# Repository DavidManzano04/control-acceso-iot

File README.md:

# Control de acceso IoT con RFID — UCEVA

Trabajo de grado **"Sistema inteligente de gestión y control de acceso al campus universitario de la UCEVA basado en tecnología IoT y de identificación automática"** (Ingeniería Electrónica, Unidad Central del Valle del Cauca).

El sistema registra la entrada y salida de los docentes de tiempo completo y ocasionales con lectores RFID, y verifica en tiempo real si cumplen su horario.

## Cómo funciona

```
Lector de ENTRADA ─┐                                           ┌─> SQLite
 (ESP32+Hikvision) │                                           │
                   ├──MQTT/TLS──> HiveMQ Cloud ──> Backend Flask
Lector de SALIDA  ─┘     ^                            │        │
 (ESP32+Hikvision)       └── permitido / denegado ────┘        └─> Dashboard web en vivo
                                                                   (Socket.IO)
```

1. El lector lee la tarjeta por Wiegand, firma la lectura con HMAC-SHA256 y la publica por MQTT sobre TLS.
2. El backend valida la firma, identifica al docente y compara la hora con su horario.
3. El lector muestra la respuesta (LED, pito y LCD) y el registro aparece al instante en el dashboard.
4. Si se cae la red, el lector guarda las lecturas y las envía cuando vuelve la conexión.

## Estructura

| Carpeta | Contenido |
| --- | --- |
| [`hardware/`](hardware) | PCB propia del nodo en KiCad: ESP32-S3, alimentación de 12 V, USB-C e interfaz Wiegand protegida, con gerbers para JLCPCB |
| [`firmware/`](firmware) | Firmware del nodo lector: ESP32, lector Hikvision por Wiegand 34, MQTT/TLS, OTA y modo sin conexión (C++, PlatformIO) |
| [`plataforma-web/`](plataforma-web) | Backend y dashboard: gestión de docentes y horarios, asistencia en tiempo real, reportes y administración de lectores (Python, Flask) |

Cada carpeta tiene su propio README con los detalles y cómo ejecutarla.

## Tecnologías

- **Hardware:** ESP32 / ESP32-S3 · lector RFID Hikvision (Wiegand 34) · LCD I2C · PCB propia diseñada en KiCad
- **Firmware:** C++ · Arduino framework · PlatformIO · LittleFS · ArduinoJson
- **Comunicación:** MQTT sobre TLS · HiveMQ Cloud · HMAC-SHA256
- **Backend y web:** Python · Flask · Flask-SocketIO · SQLite · JWT · HTML/CSS/JavaScript

> Este repositorio no incluye credenciales, la base de datos ni datos personales del prototipo. Cada parte trae un archivo de ejemplo para configurar los tuyos.

## Autores

- David Felipe Manzano Aldana
- David Santiago Vallejo Rodríguez

Ingeniería Electrónica — Unidad Central del Valle del Cauca (UCEVA), 2026.

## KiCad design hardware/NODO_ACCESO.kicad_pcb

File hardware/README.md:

# Hardware — PCB del nodo lector (v1.1)

PCB propia del nodo de control de acceso, diseñada en **KiCad**. Integra el ESP32-S3, la alimentación desde 12 V y la interfaz con el lector Hikvision por Wiegand, lista para fabricar en JLCPCB.

## Características

- **Microcontrolador:** ESP32-S3-WROOM-1-N16R8 (16 MB flash, 8 MB PSRAM), con botones de RESET y BOOT
- **Alimentación:** entrada de 12 V por bornera con fusible PTC de 1,1 A, diodo TVS SMBJ15CA y protección contra polaridad inversa; regulador conmutado AP63205 a 5 V y LDO AP7361C a 3,3 V
- **USB-C** para programación y alimentación, con protección ESD USBLC6-2SC6; diodos Schottky que eligen solos entre los 5 V del regulador y los del USB
- **Interfaz con el lector Hikvision (Wiegand):** W0, W1 y TAMPER adaptados de 5 V a 3,3 V con transistores BSS138; salidas LED verde, LED rojo y BEEP hacia el lector; protección ESD SRV05-4 en todas las líneas del lector
- **Conectores:** borneras de 5,08 mm para 12 V, lector y control del lector; header UART0 y header de expansión con 4 GPIO libres
- LEDs de encendido y de estado
- Placa de 2 capas, 82 × 70 mm, 1,6 mm de espesor
- La versión 1.1 no incluye actuadores (relé, cerradura ni talanquera): el nodo solo registra y da la respuesta en el lector

## Archivos

| Archivo | Contenido |
| --- | --- |
| `NODO_ACCESO.kicad_pro` / `.kicad_sch` / `.kicad_pcb` | Proyecto de KiCad (esquemático y PCB) |
| `Esquematico_NODO_ACCESO.pdf` | Esquemático en PDF, para verlo sin KiCad |
| `BOM_NODO_ACCESO.csv` | Lista de materiales con referencias LCSC |
| `fabricacion/` | Gerbers, BOM y archivo de posiciones (CPL) para pedir la placa ensamblada en JLCPCB |

## Nota sobre el firmware

El [firmware](../firmware) actual corre en el prototipo armado con un ESP32 DevKit. Para esta PCB con el ESP32-S3 hay que ajustar la asignación de pines según el esquemático.

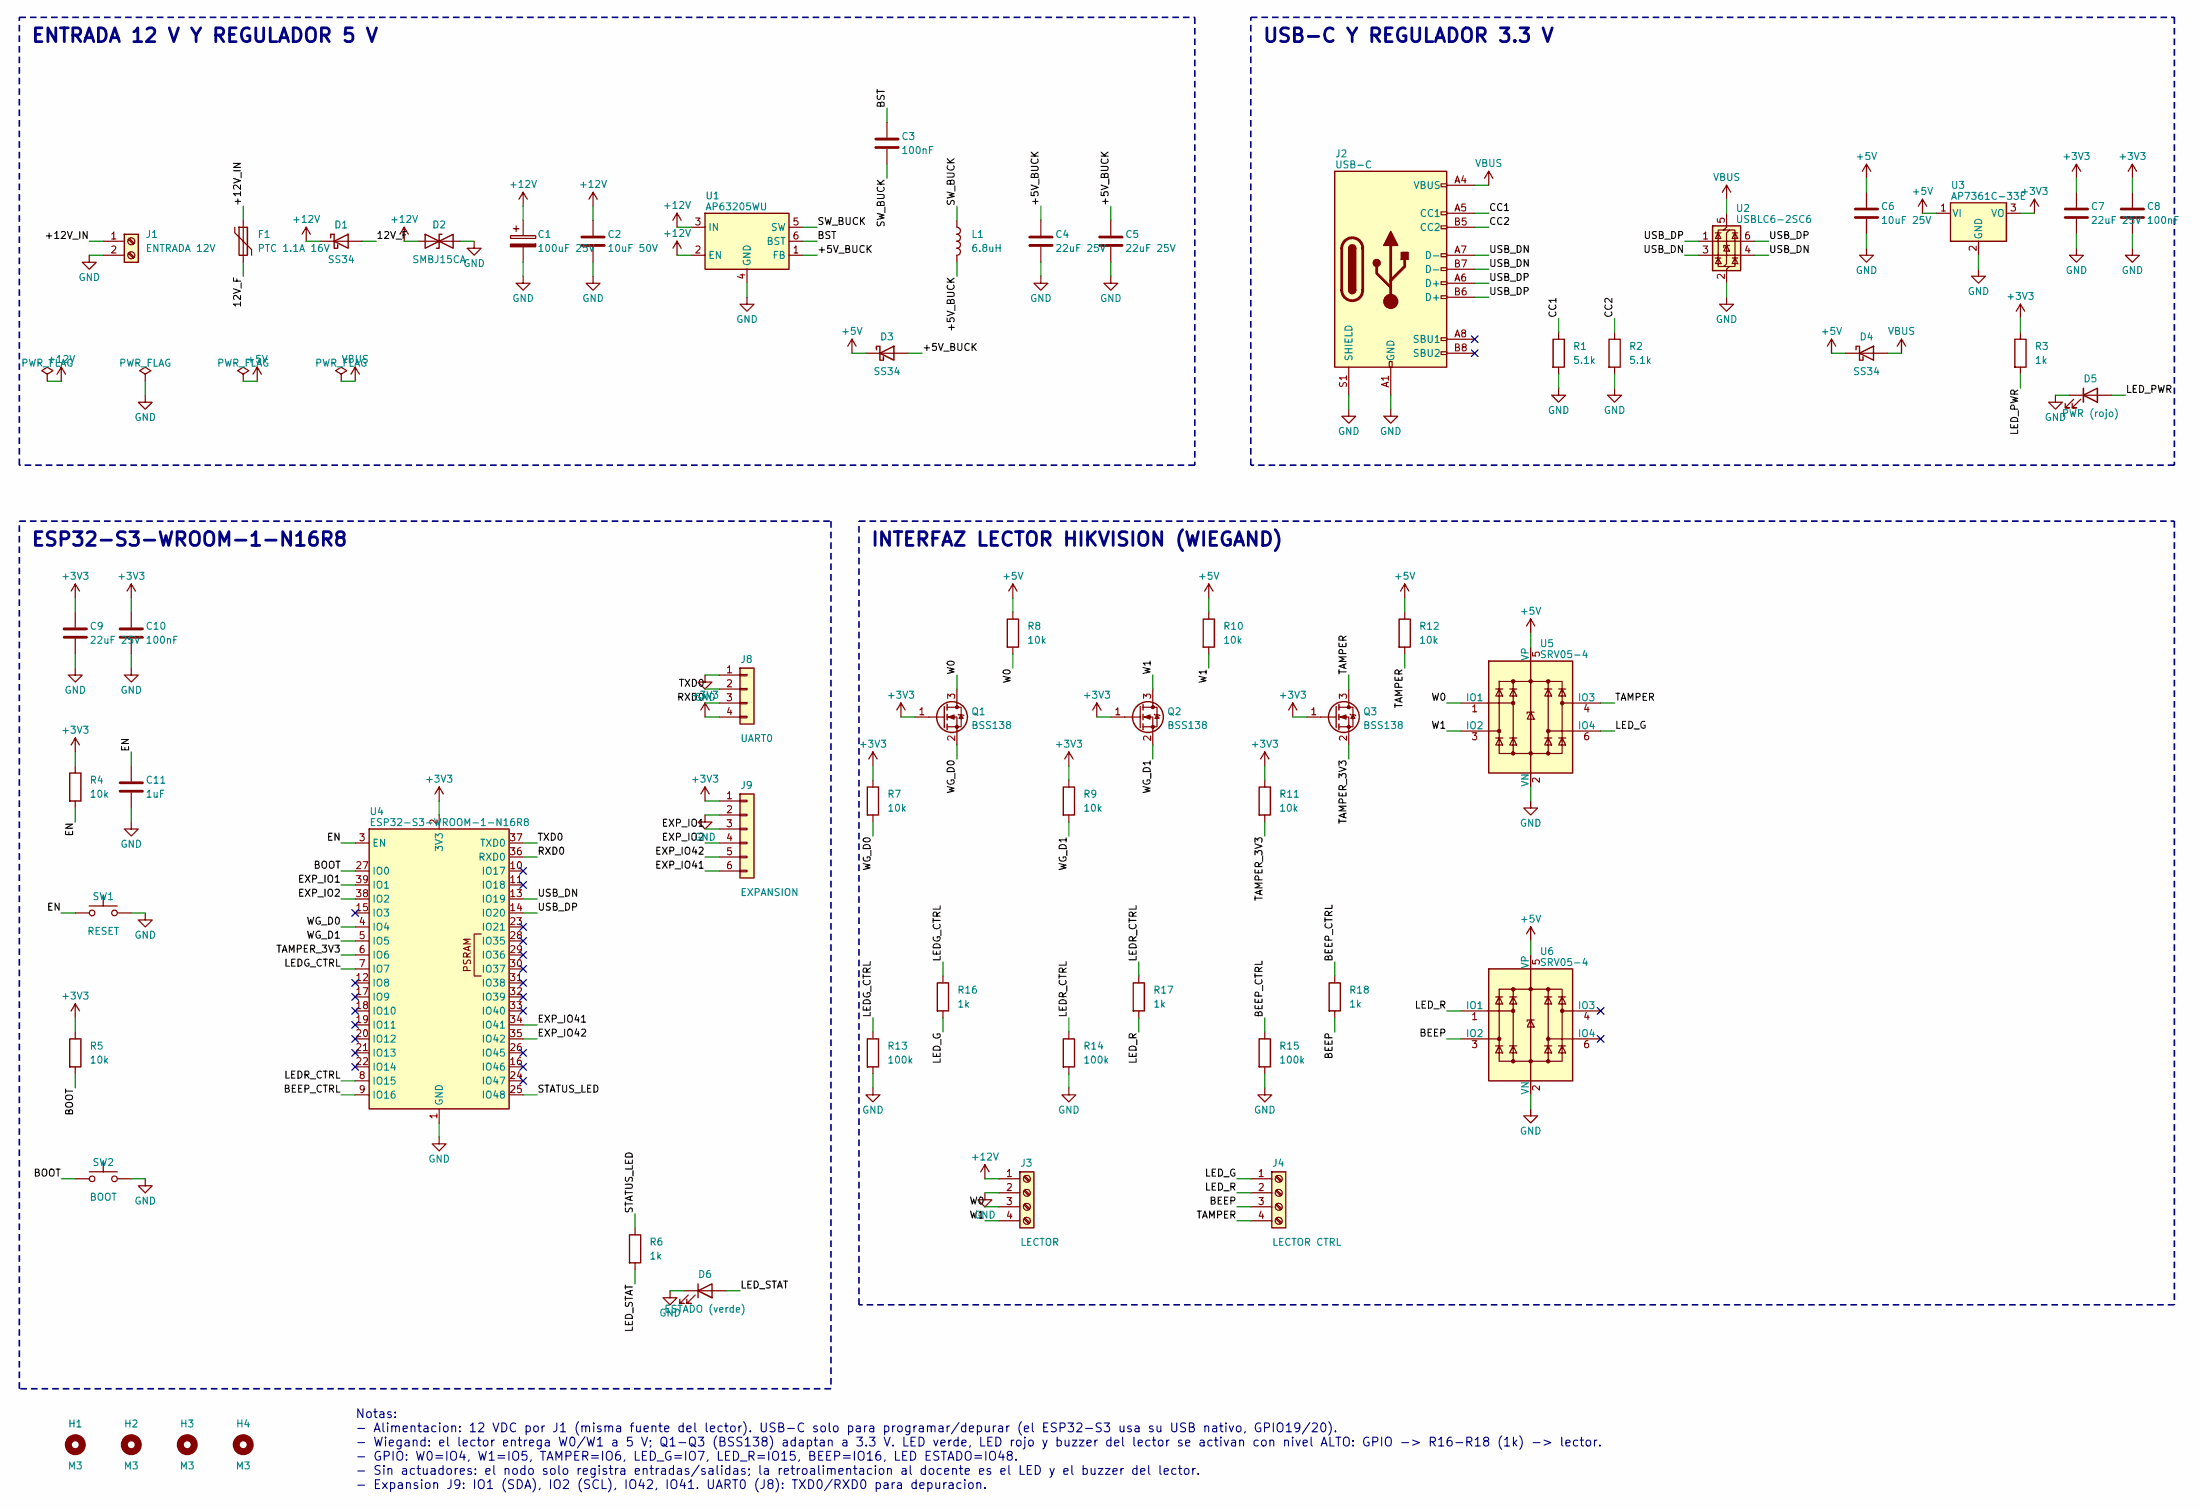
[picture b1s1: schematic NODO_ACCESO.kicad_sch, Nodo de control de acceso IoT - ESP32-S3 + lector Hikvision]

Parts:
C1: 100uF 25V; CP_Elec_6.3x7.7; MPN Aluminio SMD 100 uF 25 V 6.3 mm; LCSC C2941301
C2: 10uF 50V; C_1206_3216Metric; MPN X5R 1206 10 uF 25 V; LCSC C13585
C3, C8, C10: 100nF; C_0603_1608Metric; LCSC C14663
C4, C5: 22uF 25V; C_1206_3216Metric; LCSC C12891
C6: 10uF 25V; C_0805_2012Metric; LCSC C15850
C7, C9: 22uF 25V; C_0805_2012Metric; LCSC C45783
C11: 1uF; C_0603_1608Metric; LCSC C15849
D1: SS34; D_SMA; MPN SS34 (3 A, 40 V); LCSC C8678
D2: SMBJ15CA; D_SMB; MPN SMBJ15CA; LCSC C8829
D3, D4: SS34; D_SMA; MPN SS34; LCSC C8678
D5: PWR (rojo); LED_0603_1608Metric; LCSC C2286
D6: ESTADO (verde); LED_0603_1608Metric; LCSC C72043
F1: PTC 1.1A 16V; Fuse_1812_4532Metric; MPN JK-mSMD110-16 (1812, 1.1 A, 16 V); LCSC C369171
H1, H2, H3, H4: M3; MountingHole_3.2mm_M3
J1: ENTRADA 12V; TerminalBlock_Phoenix_MKDS-1,5-2-5.08_1x02_P5.08mm_Horizont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; MPN Phoenix MKDS 1,5/2-5,08 (1715721)
J2: USB-C; USB_C_Receptacle_HRO_TYPE-C-31-M-12; MPN Korean Hroparts TYPE-C-31-M-12; LCSC C165948
J3: LECTOR; TerminalBlock_Phoenix_MKDS-1,5-4-5.08_1x04_P5.08mm_Horizont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; MPN Phoenix MKDS 1,5/4-5,08 (1715747)
J4: LECTOR CTRL; TerminalBlock_Phoenix_MKDS-1,5-4-5.08_1x04_P5.08mm_Horizont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; MPN Phoenix MKDS 1,5/4-5,08 (1715747)
J8: UART0; PinHeader_1x04_P2.54mm_Vertical
J9: EXPANSION; PinHeader_1x06_P2.54mm_Vertical
L1: 6.8uH; L_Bourns_SRN6045TA; MPN Bourns SRN6045TA-6R8M; LCSC C135303
Q1, Q2, Q3: BSS138; SOT-23; MPN BSS138; LCSC C82045
R1, R2: 5.1k; R_0603_1608Metric; LCSC C23186
R3, R6, R16, R17, R18: 1k; R_0603_1608Metric; LCSC C21190
R4, R5, R7, R8, R9, R10, R11, R12: 10k; R_0603_1608Metric; LCSC C25804
R13, R14, R15: 100k; R_0603_1608Metric; LCSC C25803
SW1: RESET; SW_SPST_PTS810; MPN C&K PTS810 SJM 250 SMTR LFS; LCSC C221895
SW2: BOOT; SW_SPST_PTS810; MPN C&K PTS810 SJM 250 SMTR LFS; LCSC C221895
U1: AP63205WU; TSOT-23-6; MPN Diodes AP63205WU-7; LCSC C2071056
U2: USBLC6-2SC6; SOT-23-6; MPN ST USBLC6-2SC6; LCSC C7519
U3: AP7361C-33E; SOT-223-3_TabPin2; MPN Diodes AP7361C-33E-13; LCSC C500795
U4: ESP32-S3-WROOM-1-N16R8; ESP32-S3-WROOM-1; MPN Espressif ESP32-S3-WROOM-1-N16R8; LCSC C2913202
U5, U6: SRV05-4; SOT-23-6; MPN SRV05-4; LCSC C338781

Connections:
12V_F: D1.2 (A), F1.2
+3V3: C7.1, C8.1, C9.1, C10.1, J8.4, J9.1, Q1.1 (G), Q2.1 (G), Q3.1 (G), R3.1, R4.1, R5.1, R7.1, R9.1, R11.1, U3.3 (VO), U4.2 (3V3)
+5V: C6.1, D3.1 (K), D4.1 (K), R8.1, R10.1, R12.1, U3.1 (VI), U5.5 (VP), U6.5 (VP)
+5V_BUCK: C4.1, C5.1, D3.2 (A), L1.2, U1.1 (FB)
+12V: C1.1, C2.1, D1.1 (K), D2.1 (A1), J3.1, U1.2 (EN), U1.3 (IN)
+12V_IN: F1.1, J1.1
BEEP: J4.3, R18.2, U6.3 (IO2)
BEEP_CTRL: R15.1, R18.1, U4.9 (IO16)
BOOT: R5.2, SW2.1, U4.27 (IO0)
BST: C3.1, U1.6 (BST)
CC1: J2.A5 (CC1), R1.1
CC2: J2.B5 (CC2), R2.1
EN: C11.1, R4.2, SW1.1, U4.3 (EN)
EXP_IO1: J9.3, U4.39 (IO1)
EXP_IO2: J9.4, U4.38 (IO2)
EXP_IO41: J9.6, U4.34 (IO41)
EXP_IO42: J9.5, U4.35 (IO42)
GND: C1.2, C2.2, C4.2, C5.2, C6.2, C7.2, C8.2, C9.2, C10.2, C11.2, D2.2 (A2), D5.1 (K), D6.1 (K), J1.2, J2.A1 (GND), J2.A12 (GND), J2.B1 (GND), J2.B12 (GND), J2.S1 (SHIELD), J3.2, J8.1, J9.2, R1.2, R2.2, R13.2, R14.2, R15.2, SW1.2, SW2.2, U1.4 (GND), U2.2 (GND), U3.2 (GND), U4.1 (GND), U4.40 (GND), U4.41 (GND), U5.2 (VN), U6.2 (VN)
LEDG_CTRL: R13.1, R16.1, U4.7 (IO7)
LEDR_CTRL: R14.1, R17.1, U4.8 (IO15)
LED_G: J4.1, R16.2, U5.6 (IO4)
LED_PWR: D5.2 (A), R3.2
LED_R: J4.2, R17.2, U6.1 (IO1)
LED_STAT: D6.2 (A), R6.2
RXD0: J8.3, U4.36 (RXD0)
STATUS_LED: R6.1, U4.25 (IO48)
SW_BUCK: C3.2, L1.1, U1.5 (SW)
TAMPER: J4.4, Q3.3 (D), R12.2, U5.4 (IO3)
TAMPER_3V3: Q3.2 (S), R11.2, U4.6 (IO6)
TXD0: J8.2, U4.37 (TXD0)
USB_DN: J2.A7 (D-), J2.B7 (D-), U2.3 (I/O2), U2.4 (I/O2), U4.13 (IO19)
USB_DP: J2.A6 (D+), J2.B6 (D+), U2.1 (I/O1), U2.6 (I/O1), U4.14 (IO20)
VBUS: D4.2 (A), J2.A4 (VBUS), J2.A9 (VBUS), J2.B4 (VBUS), J2.B9 (VBUS), U2.5 (VBUS)
W0: J3.3, Q1.3 (D), R8.2, U5.1 (IO1)
W1: J3.4, Q2.3 (D), R10.2, U5.3 (IO2)
WG_D0: Q1.2 (S), R7.2, U4.4 (IO4)
WG_D1: Q2.2 (S), R9.2, U4.5 (IO5)

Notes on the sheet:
ENTRADA 12 V Y REGULADOR 5 V
USB-C Y REGULADOR 3.3 V
ESP32-S3-WROOM-1-N16R8
INTERFAZ LECTOR HIKVISION (WIEGAND)
Notas: - Alimentacion: 12 VDC por J1 (misma fuente del lector). USB-C solo para programar/depurar (el ESP32-S3 usa su USB nativo, GPIO19/20). - Wiegand: el lector entrega W0/W1 a 5 V; Q1-Q3 (BSS138) adaptan a 3.3 V. LED verde, LED rojo y buzzer del lector se activan con nivel ALTO: GPIO -> R16-R18 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

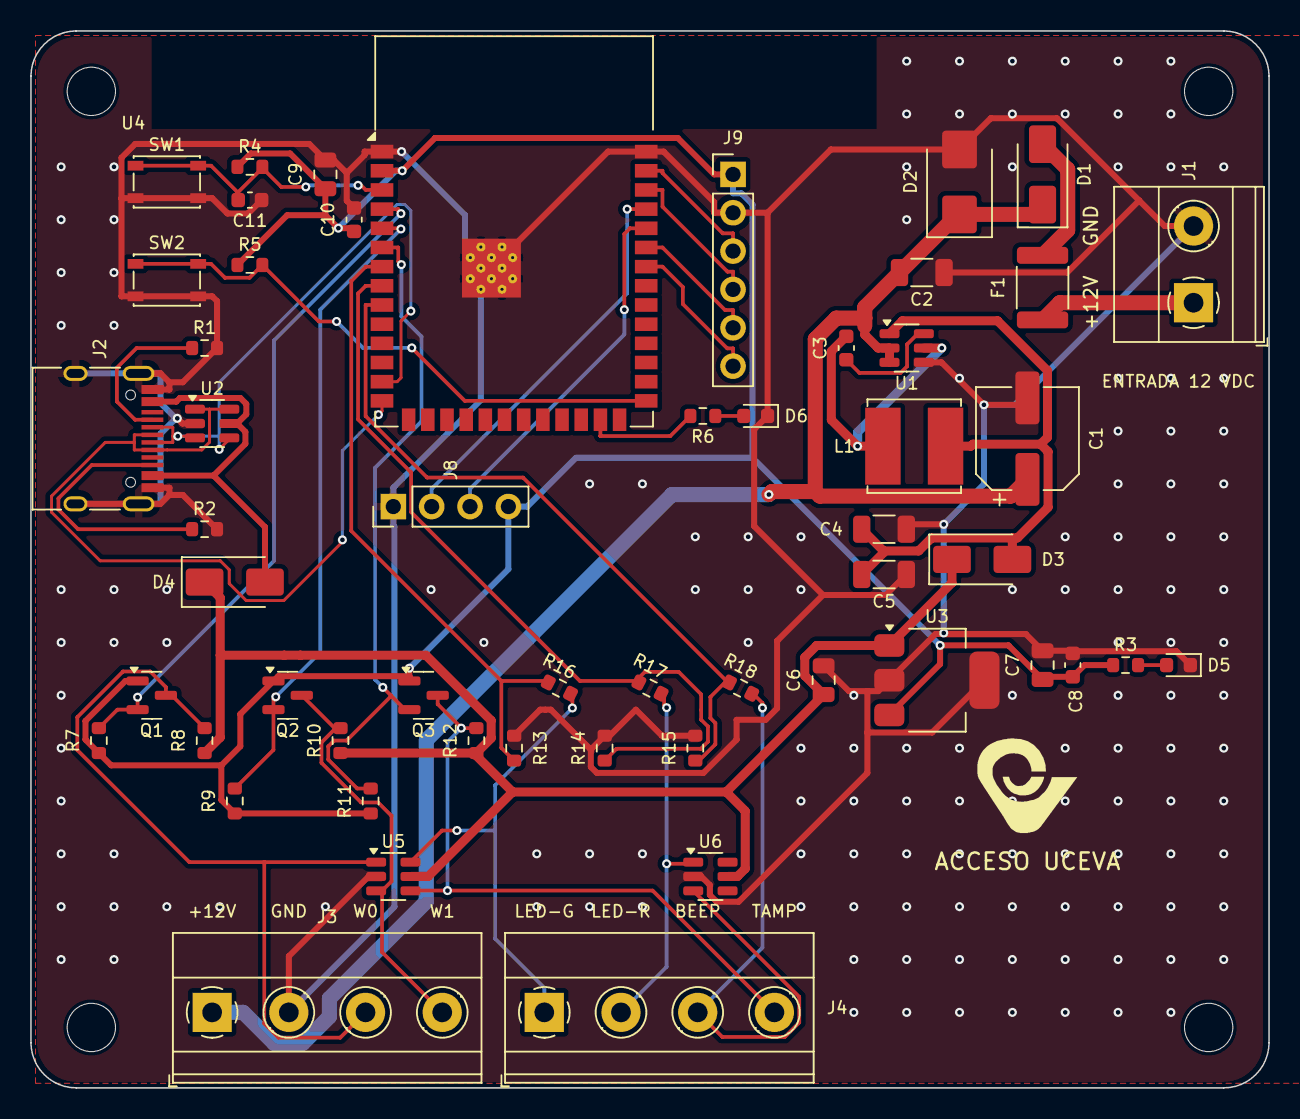
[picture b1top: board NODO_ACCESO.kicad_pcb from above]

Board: 2 copper layers, 82.0 x 70.0 mm, 58 parts (0 on the bottom side), 37 nets.

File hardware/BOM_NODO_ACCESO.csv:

Cantidad,Referencias,Valor,Huella (KiCad),Parte sugerida,LCSC
1,C1,100uF 25V,Capacitor_SMD:CP_Elec_6.3x7.7,Aluminio SMD 100 uF 25 V 6.3 mm,C2941301
1,C2,10uF 50V,Capacitor_SMD:C_1206_3216Metric,X5R 1206 10 uF 25 V,C13585
3,C3 C8 C10,100nF,Capacitor_SMD:C_0603_1608Metric,,C14663
2,C4 C5,22uF 25V,Capacitor_SMD:C_1206_3216Metric,,C12891
1,C6,10uF 25V,Capacitor_SMD:C_0805_2012Metric,,C15850
2,C7 C9,22uF 25V,Capacitor_SMD:C_0805_2012Metric,,C45783
1,C11,1uF,Capacitor_SMD:C_0603_1608Metric,,C15849
1,D1,SS34,Diode_SMD:D_SMA,"SS34 (3 A, 40 V)",C8678
1,D2,SMBJ15CA,Diode_SMD:D_SMB,SMBJ15CA,C8829
2,D3 D4,SS34,Diode_SMD:D_SMA,SS34,C8678
1,D5,PWR (rojo),LED_SMD:LED_0603_1608Metric,,C2286
1,D6,ESTADO (verde),LED_SMD:LED_0603_1608Metric,,C72043
1,F1,PTC 1.1A 16V,Fuse:Fuse_1812_4532Metric,"JK-mSMD110-16 (1812, 1.1 A, 16 V)",C369171
1,J1,ENTRADA 12V,"TerminalBlock_Phoenix:TerminalBlock_Phoenix_MKDS-1,5-2-5.08_1x02_P5.08mm_Horizontal","Phoenix MKDS 1,5/2-5,08 (1715721)",(soldar a mano)
1,J2,USB-C,Connector_USB:USB_C_Receptacle_HRO_TYPE-C-31-M-12,Korean Hroparts TYPE-C-31-M-12,C165948
1,J3,LECTOR,"TerminalBlock_Phoenix:TerminalBlock_Phoenix_MKDS-1,5-4-5.08_1x04_P5.08mm_Horizontal","Phoenix MKDS 1,5/4-5,08 (1715747)",(soldar a mano)
1,J4,LECTOR CTRL,"TerminalBlock_Phoenix:TerminalBlock_Phoenix_MKDS-1,5-4-5.08_1x04_P5.08mm_Horizontal","Phoenix MKDS 1,5/4-5,08 (1715747)",(soldar a mano)
1,J8,UART0,Connector_PinHeader_2.54mm:PinHeader_1x04_P2.54mm_Vertical,,(soldar a mano)
1,J9,EXPANSION,Connector_PinHeader_2.54mm:PinHeader_1x06_P2.54mm_Vertical,,(soldar a mano)
1,L1,6.8uH,Inductor_SMD:L_Bourns_SRN6045TA,Bourns SRN6045TA-6R8M,C135303
3,Q1 Q2 Q3,BSS138,Package_TO_SOT_SMD:SOT-23,BSS138,C82045
2,R1 R2,5.1k,Resistor_SMD:R_0603_1608Metric,,C23186
2,R3 R6,1k,Resistor_SMD:R_0603_1608Metric,,C21190
3,R16 R17 R18,1k,Resistor_SMD:R_0603_1608Metric,"Serie GPIO -> lector (OK/ERR/BEEP, activo en alto)",C21190
8,R4 R5 R7 R8 R9 R10 R11 R12,10k,Resistor_SMD:R_0603_1608Metric,,C25804
3,R13 R14 R15,100k,Resistor_SMD:R_0603_1608Metric,,C25803
1,SW1,RESET,Button_Switch_SMD:SW_SPST_PTS810,C&K PTS810 SJM 250 SMTR LFS,C221895
1,SW2,BOOT,Button_Switch_SMD:SW_SPST_PTS810,C&K PTS810 SJM 250 SMTR LFS,C221895
1,U1,AP63205WU,Package_TO_SOT_SMD:TSOT-23-6,Diodes AP63205WU-7,C2071056
1,U2,USBLC6-2SC6,Package_TO_SOT_SMD:SOT-23-6,ST USBLC6-2SC6,C7519
1,U3,AP7361C-33E,Package_TO_SOT_SMD:SOT-223-3_TabPin2,Diodes AP7361C-33E-13,C500795
1,U4,ESP32-S3-WROOM-1-N16R8,RF_Module:ESP32-S3-WROOM-1,Espressif ESP32-S3-WROOM-1-N16R8,C2913202
2,U5 U6,SRV05-4,Package_TO_SOT_SMD:SOT-23-6,SRV05-4,C338781

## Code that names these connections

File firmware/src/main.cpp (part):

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// Respuesta al lector por el módulo ULN2003 (GPIO en HIGH = línea del lector a GND):
//   OK   (cable marrón, LED verde) -> IN2 <- GPIO 16 (RX2)
//   ERR  (cable naranja, LED rojo) -> IN3 <- GPIO 17 (TX2)
//   BEEP (cable morado, pito)      -> IN1 <- GPIO 4
// LCD I2C: SDA=21, SCL=22
#define WG_D0_PIN 32
#define WG_D1_PIN 33
#define LECTOR_OK_PIN 16
#define LECTOR_ERR_PIN 17
#define LECTOR_BEEP_PIN 4
#define SERVO_PIN 13
#define LED_R_PIN 25
#define LED_G_PIN 26
#define LED_B_PIN 27
#define BUZZER_PIN 14

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// Los LEDs y el buzzer locales se repiten en el lector Hikvision:
// verde -> OK, rojo -> ERR, pitido -> BEEP. Azul no tiene equivalente en el lector.
void ledOff() {
  digitalWrite(LED_R_PIN, LOW); digitalWrite(LED_G_PIN, LOW); digitalWrite(LED_B_PIN, LOW);
  digitalWrite(LECTOR_OK_PIN, LOW); digitalWrite(LECTOR_ERR_PIN, LOW);
}
void ledVerde() { ledOff(); digitalWrite(LED_G_PIN, HIGH); digitalWrite(LECTOR_OK_PIN, HIGH); }
void ledRojo() { ledOff(); digitalWrite(LED_R_PIN, HIGH); digitalWrite(LECTOR_ERR_PIN, HIGH); }
void ledAzul() { ledOff(); digitalWrite(LED_B_PIN, HIGH); }
void beep(int veces, int ms) {
  for (int i = 0; i < veces; i++) {
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// GPIO 32 y 33 se leen directo del registro GPIO_IN1 (bits 0 y 1).
void IRAM_ATTR wgPulso(bool esUno) {
  uint32_t entrada = REG_READ(GPIO_IN1_REG);
  bool d0Alto = entrada & (1UL << (WG_D0_PIN - 32));
  bool d1Alto = entrada & (1UL << (WG_D1_PIN - 32));
  bool propioAlto = esUno ? d1Alto : d0Alto;
  bool otroAlto = esUno ? d0Alto : d1Alto;
  uint32_t ahora = micros();
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  if (n == 0) return;
  Serial.printf("[WIEGAND] %u pulsos de ruido ignorados. En reposo D0=%d D1=%d (deben estar en 1). "
                "Revise GND comun y que el punto medio de cada divisor marque ~3,3 V\n",
                (unsigned int)n, digitalRead(WG_D0_PIN), digitalRead(WG_D1_PIN));
}

void iniciarWiegand() {
  pinMode(WG_D0_PIN, INPUT);
  pinMode(WG_D1_PIN, INPUT);
  attachInterrupt(digitalPinToInterrupt(WG_D0_PIN), wgPulsoD0, FALLING);
  attachInterrupt(digitalPinToInterrupt(WG_D1_PIN), wgPulsoD1, FALLING);
  Serial.printf("[WIEGAND] Lineas en reposo: D0(GPIO%d)=%d D1(GPIO%d)=%d (deben estar en 1)\n", WG_D0_PIN,
                digitalRead(WG_D0_PIN), WG_D1_PIN, digitalRead(WG_D1_PIN));
}

void descartarWiegand() {
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  if (c == "err" || c == "test") probarSalida("ERR / LED rojo (naranja)", LECTOR_ERR_PIN, 2000);
  if (c == "test") delay(500);
  if (c == "beep" || c == "test") {
    for (int i = 0; i < 3; i++) { probarSalida("BEEP / pito (morado)", LECTOR_BEEP_PIN, 300); delay(300); }
  }
}

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
  iniciarWiegand();

  pinMode(LED_R_PIN, OUTPUT);
  pinMode(LED_G_PIN, OUTPUT);
  pinMode(LED_B_PIN, OUTPUT);
  pinMode(BUZZER_PIN, OUTPUT);
  servo.attach(SERVO_PIN);
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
